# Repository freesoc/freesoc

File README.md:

freesoc
=======

freeSoC Board Layouts and Schematics

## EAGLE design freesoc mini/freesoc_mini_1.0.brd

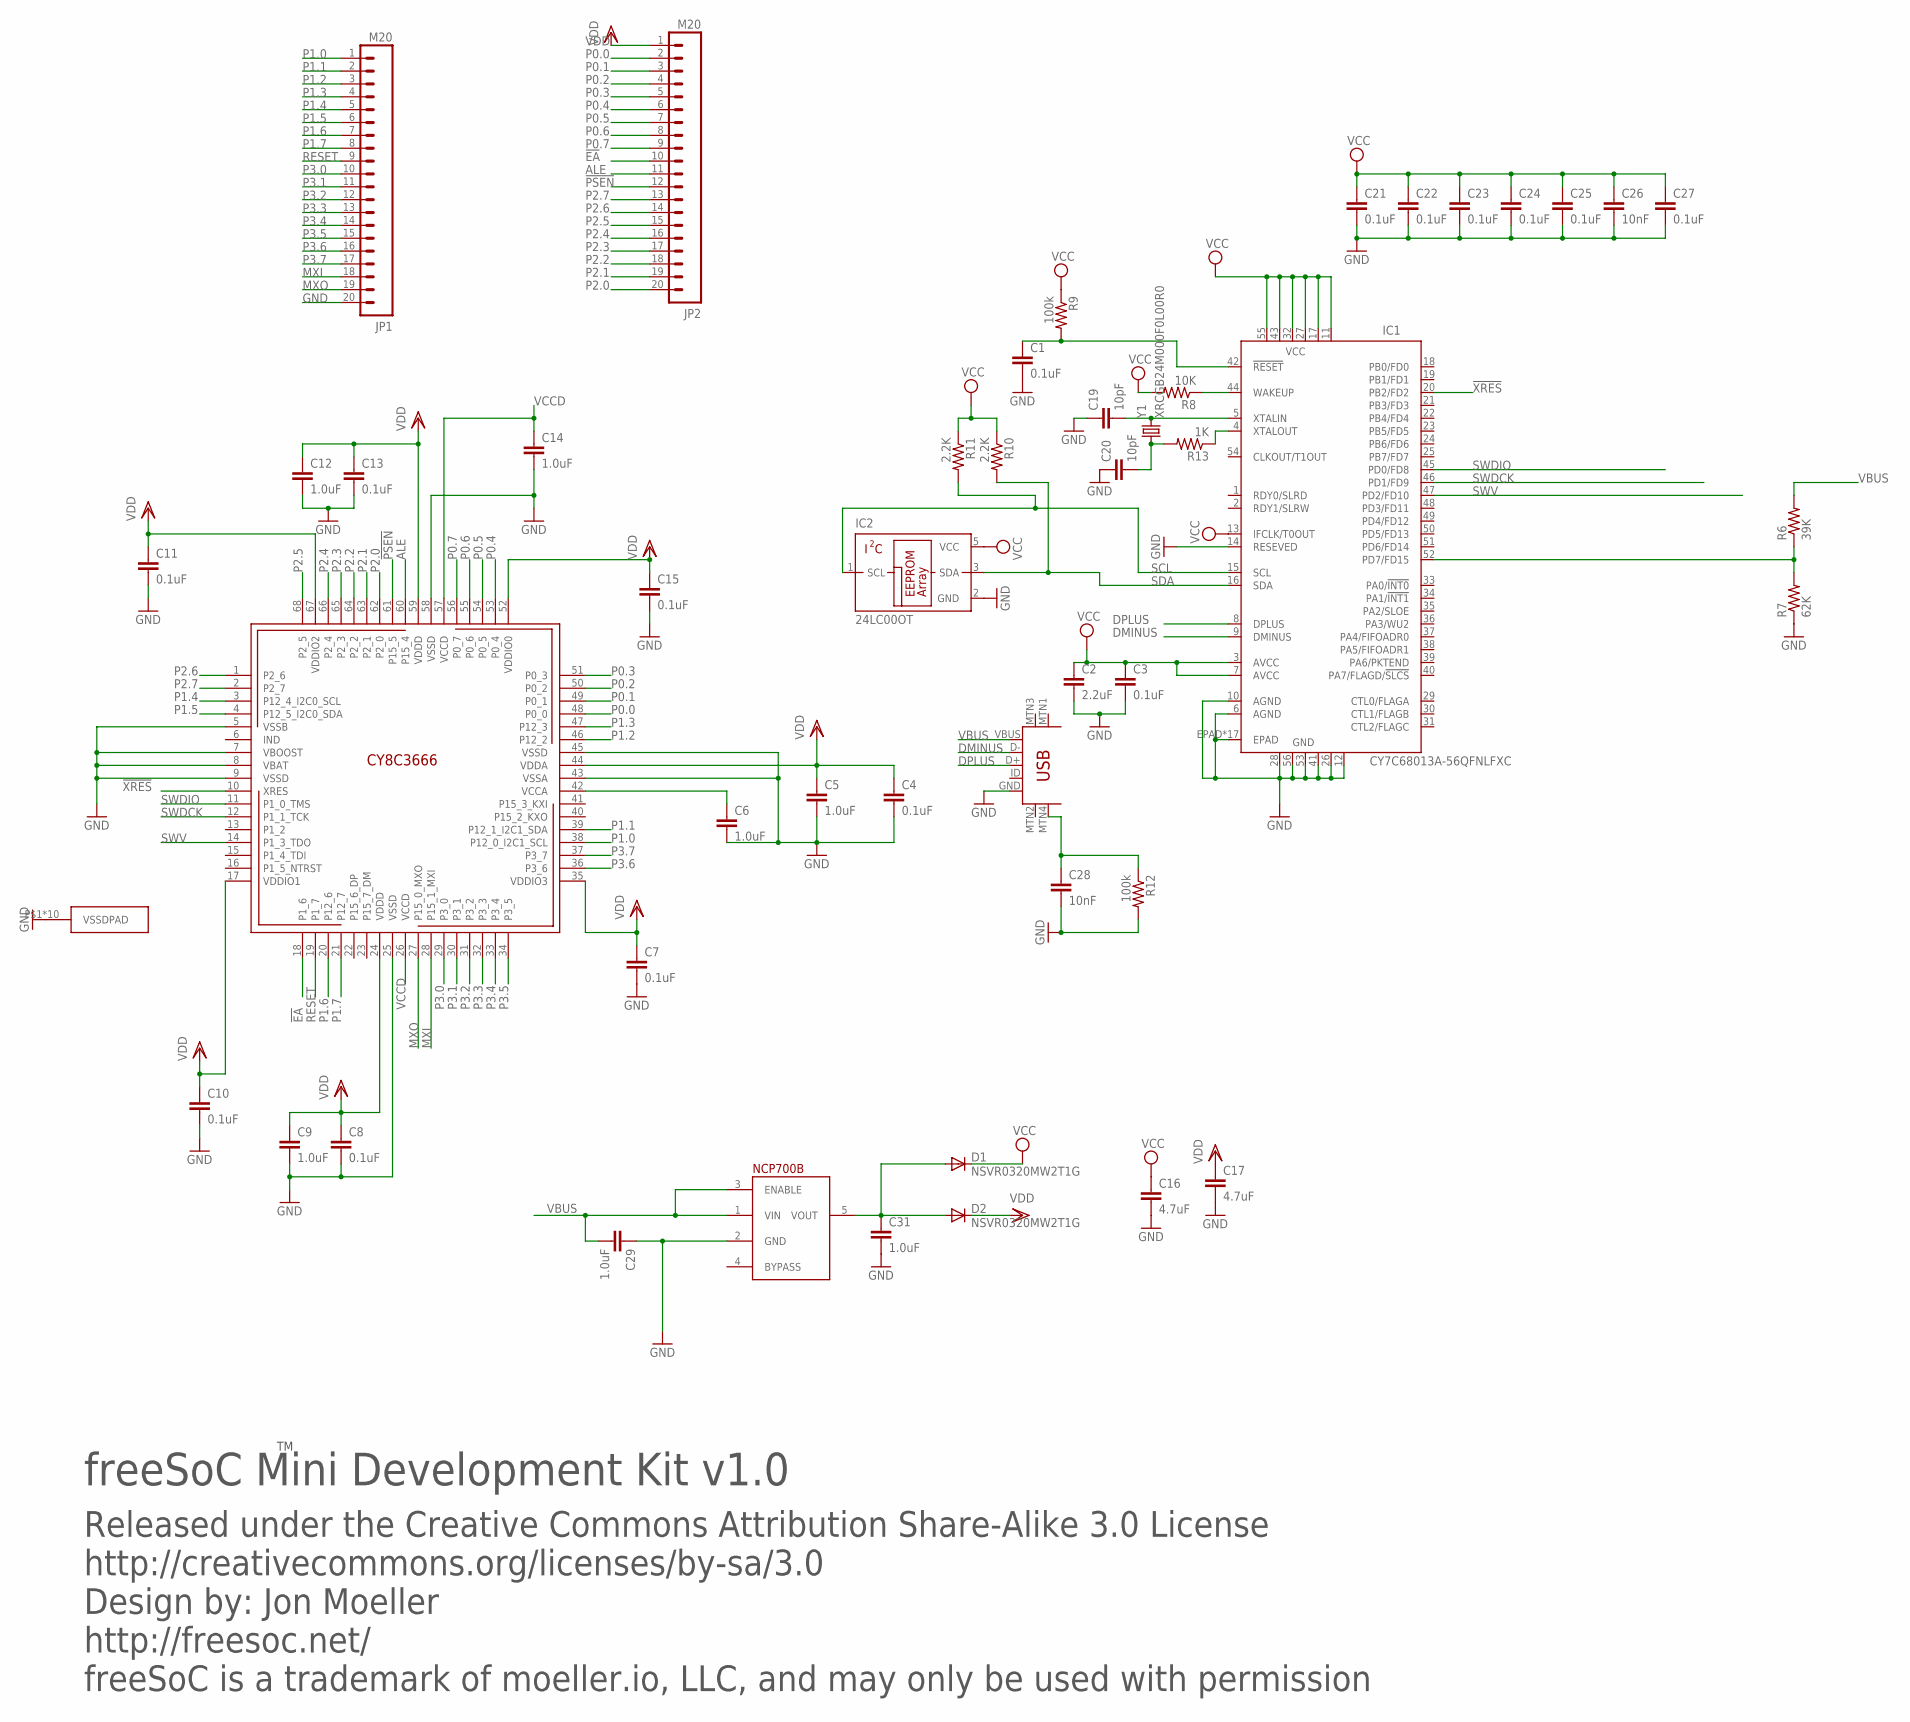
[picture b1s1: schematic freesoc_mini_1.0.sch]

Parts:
C1, C3, C4, C7, C8, C10, C11, C13, C15, C21, C22, C23, C24, C25, C27: 0.1uF; 0402-CAP
C2: 2.2uF; 0402-CAP
C5, C6, C9, C12, C14, C29, C31: 1.0uF; 0402-CAP
C16, C17: 4.7uF; 0603-CAP
C19, C20: 10pF; 0402-CAP
C26, C28: 10nF; 0402-CAP
D1, D2: NSVR0320MW2T1G; SOD-323
IC1: CY7C68013A-56QFNLFXC; QFN56
IC2: 24LC00OT; SOT23-5L
JP1, JP2: M20; 1X20
R6: 39K; 0402-RES
R7: 62K; 0402-RES
R8: 10K; 0402-RES
R9, R12: 100k; 0402-RES
R10, R11: 2.2K; 0402-RES
R13: 1K; 0402-RES
U$1: CY8C3X66LTI; QFN-68
U$3: FAN2558S36X; TSOP-5
USB-MINIB: USB-MINIB-5PIN; USB-MINIB
Y1: XRCGB24M000F0L00R0; CRYSTAL_RESONATOR

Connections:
!EA: JP2.10, U$1.18 (P1_6)
!PSEN: JP2.12, U$1.61 (P15_5)
!XRES: IC1.20 (PB2/FD2), U$1.10 (XRES)
ALE: JP2.11, U$1.60 (P15_4)
DMINUS: IC1.9 (DMINUS), USB-MINIB.D-
DPLUS: IC1.8 (DPLUS), USB-MINIB.D+
GND: C1.2, C2.2, C3.2, C4.2, C5.2, C6.2, C7.2, C8.2, C9.2, C10.2, C11.2, C12.2, C13.2, C14.2, C15.2, C16.2, C17.2, C19.1, C20.1, C21.2, C22.2, C23.2, C24.2, C25.2, C26.2, C27.2, C28.2, C29.1, C31.2, IC1.6 (AGND), IC1.10 (AGND), IC1.12 (GND), IC1.14 (RESEVED), IC1.26 (GND), IC1.28 (GND), IC1.41 (GND), IC1.53 (GND), IC1.56 (GND), IC1.EPAD, IC1.P$1 (EPAD), IC1.P$2 (EPAD), IC1.P$3 (EPAD), IC1.P$4 (EPAD), IC1.P$5 (EPAD), IC1.P$6 (EPAD), IC1.P$7 (EPAD), IC1.P$8 (EPAD), IC1.P$9 (EPAD), IC1.P$10 (EPAD), IC1.P$11 (EPAD), IC1.P$12 (EPAD), IC1.P$13 (EPAD), IC1.P$14 (EPAD), IC1.P$15 (EPAD), IC1.P$16 (EPAD), IC2.2 (GND), JP1.20, R7.1, R12.2, U$1.5 (VSSB), U$1.7 (VBOOST), U$1.8 (VBAT), U$1.9 (VSSD), U$1.25 (VSSD), U$1.43 (VSSA), U$1.45 (VSSD), U$1.58 (VSSD), U$1.P$1 (VSSDPAD), U$1.P$2 (VSSDPAD), U$1.P$3 (VSSDPAD), U$1.P$4 (VSSDPAD), U$1.P$5 (VSSDPAD), U$1.P$6 (VSSDPAD), U$1.P$7 (VSSDPAD), U$1.P$8 (VSSDPAD), U$1.P$9 (VSSDPAD), U$1.PAD (VSSDPAD), U$3.2 (GND), USB-MINIB.GND
MXI: JP1.18, U$1.28 (P15_1_MXI)
MXO: JP1.19, U$1.27 (P15_0_MXO)
unnamed: IC1.52 (PD7/FD15), R6.1, R7.2
unnamed: IC1.44 (WAKEUP), R8.1
unnamed: C1.1, IC1.42 (!RESET), R9.2
unnamed: C28.1, R12.1, USB-MINIB.MTN4
unnamed: IC1.4 (XTALOUT), R13.1
unnamed: C20.2, R13.2, Y1.P$1 (1)
unnamed: C19.2, IC1.5 (XTALIN), Y1.P$4 (2)
unnamed: C6.1, U$1.42 (VCCA)
P0.0: JP2.2, U$1.48 (P0_0)
P0.1: JP2.3, U$1.49 (P0_1)
P0.2: JP2.4, U$1.50 (P0_2)
P0.3: JP2.5, U$1.51 (P0_3)
P0.4: JP2.6, U$1.53 (P0_4)
P0.5: JP2.7, U$1.54 (P0_5)
P0.6: JP2.8, U$1.55 (P0_6)
P0.7: JP2.9, U$1.56 (P0_7)
P1.0: JP1.1, U$1.38 (P12_0_I2C1_SCL)
P1.1: JP1.2, U$1.39 (P12_1_I2C1_SDA)
P1.2: JP1.3, U$1.46 (P12_2)
P1.3: JP1.4, U$1.47 (P12_3)
P1.4: JP1.5, U$1.3 (P12_4_I2C0_SCL)
P1.5: JP1.6, U$1.4 (P12_5_I2C0_SDA)
P1.6: JP1.7, U$1.20 (P12_6)
P1.7: JP1.8, U$1.21 (P12_7)
P2.0: JP2.20, U$1.62 (P2_0)
P2.1: JP2.19, U$1.63 (P2_1)
P2.2: JP2.18, U$1.64 (P2_2)
P2.3: JP2.17, U$1.65 (P2_3)
P2.4: JP2.16, U$1.66 (P2_4)
P2.5: JP2.15, U$1.68 (P2_5)
P2.6: JP2.14, U$1.1 (P2_6)
P2.7: JP2.13, U$1.2 (P2_7)
P3.0: JP1.10, U$1.29 (P3_0)
P3.1: JP1.11, U$1.30 (P3_1)
P3.2: JP1.12, U$1.31 (P3_2)
P3.3: JP1.13, U$1.32 (P3_3)
P3.4: JP1.14, U$1.33 (P3_4)
P3.5: JP1.15, U$1.34 (P3_5)
P3.6: JP1.16, U$1.36 (P3_6)
P3.7: JP1.17, U$1.37 (P3_7)
RESET: JP1.9, U$1.19 (P1_7)
SCL: IC1.15 (SCL), IC2.1 (SCL), R11.2
SDA: IC1.16 (SDA), IC2.3 (SDA), R10.2
SWDCK: IC1.46 (PD1/FD9), U$1.12 (P1_1_TCK)
SWDIO: IC1.45 (PD0/FD8), U$1.11 (P1_0_TMS)
SWV: IC1.47 (PD2/FD10), U$1.14 (P1_3_TDO)
VBUS: C29.2, R6.2, U$3.1 (VIN), U$3.3 (ENABLE), USB-MINIB.VBUS
VCC: C2.1, C3.1, C16.1, C21.1, C22.1, C23.1, C24.1, C25.1, C26.1, C27.1, D1.1 (C), IC1.3 (AVCC), IC1.7 (AVCC), IC1.11 (VCC), IC1.13 (IFCLK/T0OUT), IC1.17 (VCC), IC1.27 (VCC), IC1.32 (VCC), IC1.43 (VCC), IC1.55 (VCC), IC2.5 (VCC), R8.2, R9.1, R10.1, R11.1
VCCD: C14.1, U$1.26 (VCCD), U$1.57 (VCCD)
VDD: C4.1, C5.1, C7.1, C8.1, C9.1, C10.1, C11.1, C12.1, C13.1, C15.1, C17.1, D2.1 (C), JP2.1, U$1.17 (VDDIO1), U$1.24 (VDDD), U$1.35 (VDDIO3), U$1.44 (VDDA), U$1.52 (VDDIO0), U$1.59 (VDDD), U$1.67 (VDDIO2)
VOUT: C31.1, D1.2 (A), D2.2 (A), U$3.5 (VOUT)

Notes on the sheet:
Released under the Creative Commons Attribution Share-Alike 3.0 License
http://creativecommons.org/licenses/by-sa/3.0
Design by: Jon Moeller
http://freesoc.net/
freeSoC is a trademark of moeller.io, LLC, and may only be used with permission
freeSoC Mini Development Kit v1.0

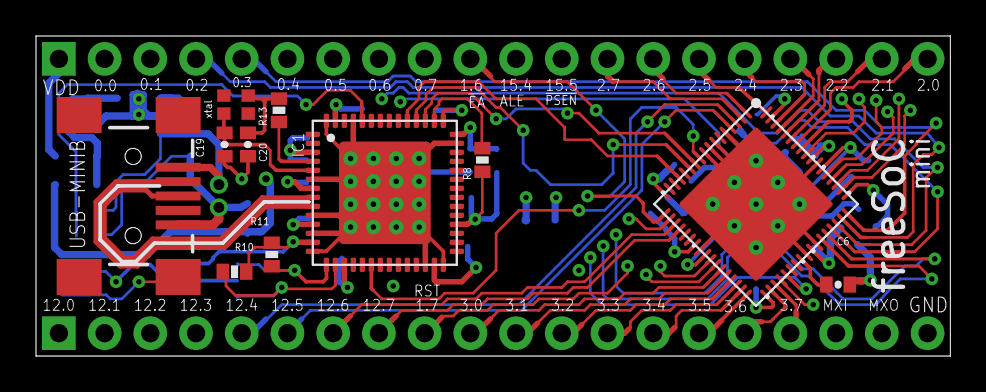
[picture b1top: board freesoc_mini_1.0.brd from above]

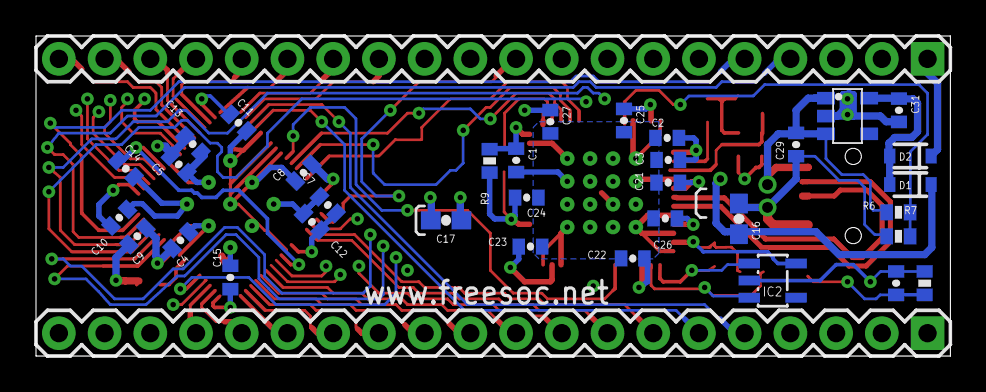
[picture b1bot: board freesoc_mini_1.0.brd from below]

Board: 4 copper layers, 50.8 x 17.8 mm, 47 parts (36 on the bottom side), 60 nets.

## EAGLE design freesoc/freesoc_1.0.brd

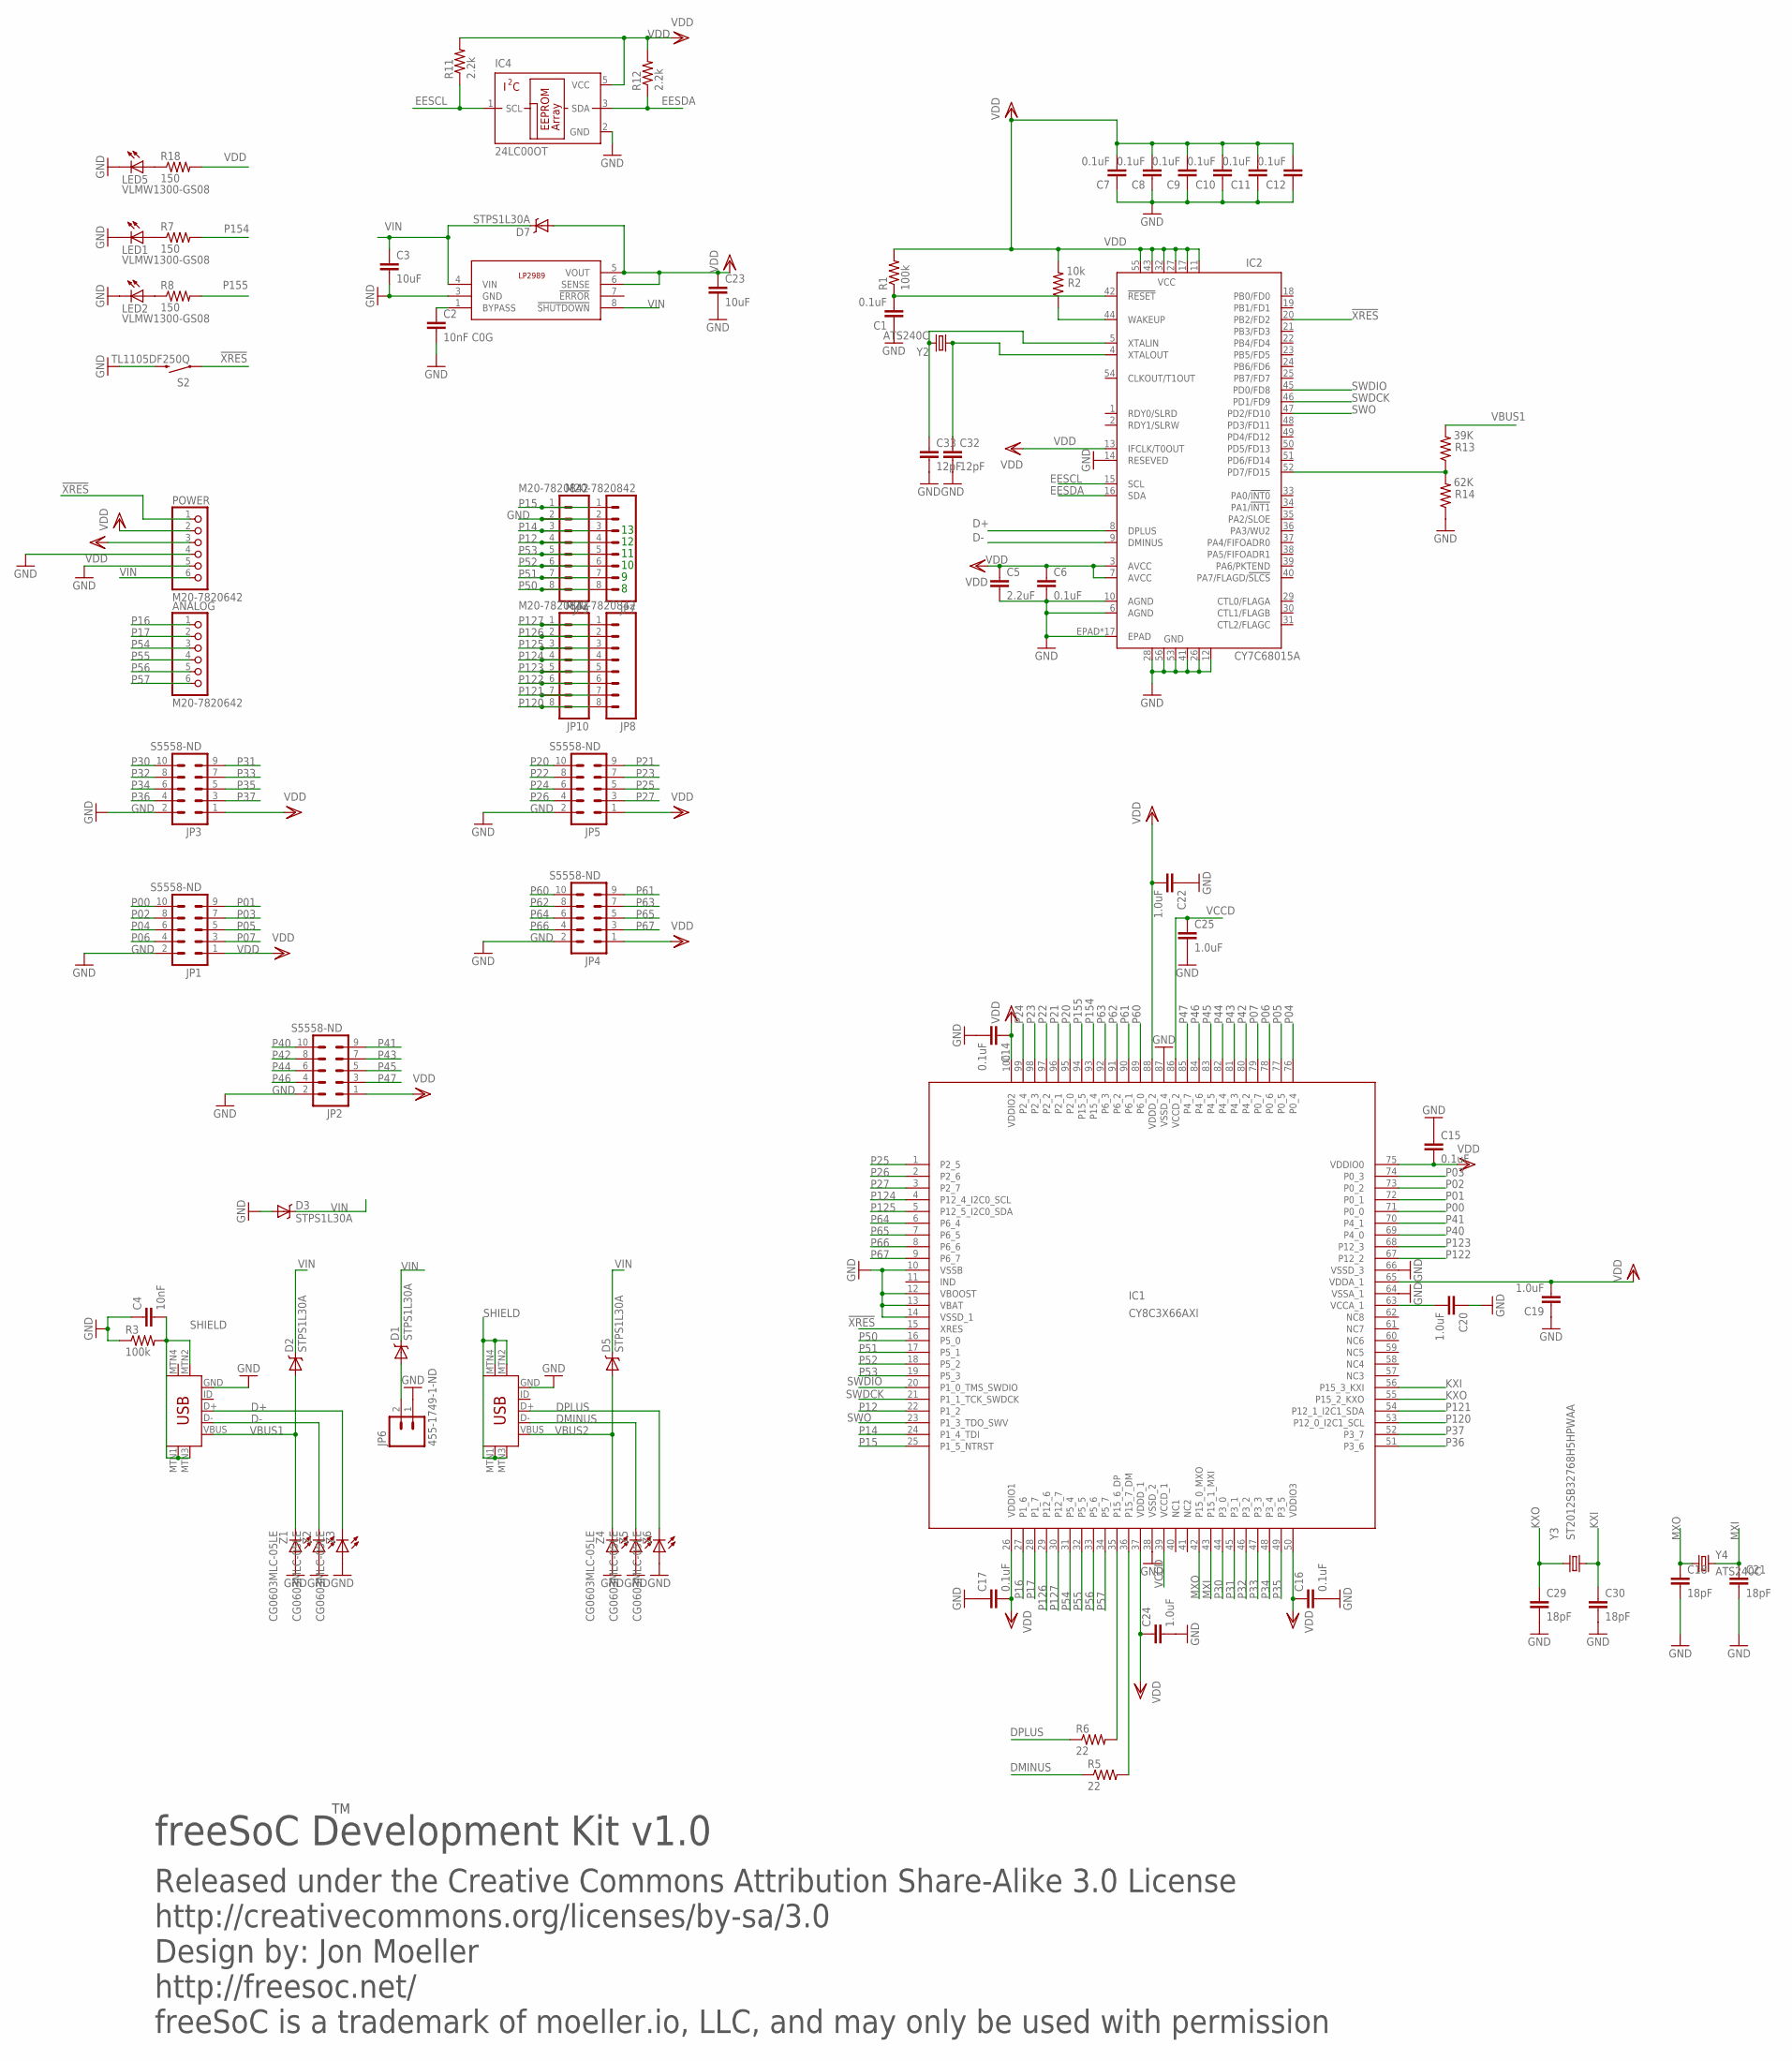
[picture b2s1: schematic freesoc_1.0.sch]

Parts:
ANALOG: M20-7820642; 1X06
C1, C6, C7, C8, C9, C10, C11, C12, C14, C15, C16, C17: 0.1uF; 0402-CAP
C2: 10nF C0G; 0402-CAP
C3, C23: 10uF; 1206
C4: 10nF; 0402-CAP
C5: 2.2uF; 0603-CAP
C18, C21, C29, C30: 18pF; 0402-CAP
C19, C20, C22, C24, C25: 1.0uF; 0402-CAP
C32, C33: 12pF; 0402-CAP
D1, D2, D3, D5, D7: STPS1L30A; SMA-DIODE
IC1: CY8C3X66AXI; TQFP-100
IC2: CY7C68015A; QFN56
IC4: 24LC00OT; SOT23-5L
JP1, JP2, JP3, JP4, JP5: S5558-ND; 2X5-RAF
JP6: 455-1749-1-ND; JST-2-SMD
JP7, JP8, JP9, JP10: M20-7820842; 1X08
LED1, LED2, LED5: VLMW1300-GS08; LED-0603
POWER: M20-7820642; 1X06
R1, R3: 100k; 0402-RES
R2: 10k; 0402-RES
R5, R6: 22; 0805
R7, R8, R18: 150; 0603-RES
R11, R12: 2.2k; 0402-RES
R13: 39K; 0402-RES
R14: 62K; 0402-RES
S2: TL1105DF250Q; TACTILE-PTH
U$1: LP2989; SO08
U$5, U$6: USB-MINIB-5PIN; USB-MINIB
Y2, Y4: ATS240C; HC49US
Y3: ST2012SB32768H5HPWAA; ST2012B
Z1, Z2, Z3, Z4, Z5, Z6: CG0603MLC-05LE; LED-0603

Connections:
!XRES: IC1.15 (XRES), IC2.20 (PB2/FD2), POWER.1, S2.1
D+: IC2.8 (DPLUS), U$5.D+, Z3.C
D-: IC2.9 (DMINUS), U$5.D-, Z2.C
DMINUS: R5.1, U$6.D-, Z5.C
DPLUS: R6.1, U$6.D+, Z6.C
EESCL: IC2.15 (SCL), IC4.1 (SCL), R11.1
EESDA: IC2.16 (SDA), IC4.3 (SDA), R12.1
GND: C1.1, C2.2, C3.2, C4.1, C5.2, C6.2, C7.1, C8.1, C9.1, C10.1, C11.1, C12.1, C14.2, C15.1, C16.2, C17.1, C18.2, C19.1, C20.1, C21.2, C22.1, C23.2, C24.2, C25.2, C29.2, C30.2, C32.2, C33.2, D3.A, IC1.10 (VSSB), IC1.12 (VBOOST), IC1.13 (VBAT), IC1.14 (VSSD_1), IC1.38 (VSSD_2), IC1.64 (VSSA_1), IC1.66 (VSSD_3), IC1.87 (VSSD_4), IC2.6 (AGND), IC2.10 (AGND), IC2.12 (GND), IC2.14 (RESEVED), IC2.26 (GND), IC2.28 (GND), IC2.41 (GND), IC2.53 (GND), IC2.56 (GND), IC2.EPAD, IC2.P$1 (EPAD), IC2.P$2 (EPAD), IC2.P$3 (EPAD), IC2.P$4 (EPAD), IC2.P$5 (EPAD), IC2.P$6 (EPAD), IC2.P$7 (EPAD), IC2.P$8 (EPAD), IC2.P$9 (EPAD), IC2.P$10 (EPAD), IC2.P$11 (EPAD), IC2.P$12 (EPAD), IC2.P$13 (EPAD), IC2.P$14 (EPAD), IC2.P$15 (EPAD), IC2.P$16 (EPAD), IC4.2 (GND), JP1.2, JP2.2, JP3.2, JP4.2, JP5.2, JP6.1, JP7.2, JP9.2, LED1.C, LED2.C, LED5.C, POWER.4, POWER.5, R3.1, R14.1, S2.3 (2), U$1.3 (GND), U$5.GND, U$6.GND, Z1.A, Z2.A, Z3.A, Z4.A, Z5.A, Z6.A
KXI: C30.1, IC1.56 (P15_3_KXI), Y3.P$2 (2)
KXO: C29.1, IC1.55 (P15_2_KXO), Y3.P$1 (1)
MXI: C21.1, IC1.43 (P15_1_MXI), Y4.2
MXO: C18.1, IC1.42 (P15_0_MXO), Y4.1
unnamed: C1.2, IC2.42 (!RESET), R1.1
unnamed: D1.A, JP6.2
unnamed: IC2.44 (WAKEUP), R2.1
unnamed: C20.2, IC1.63 (VCCA_1)
unnamed: IC1.35 (P15_6_DP), R6.2
unnamed: IC1.36 (P15_7_DM), R5.2
unnamed: LED1.A, R7.1
unnamed: LED2.A, R8.1
unnamed: C2.1, U$1.1 (BYPASS)
unnamed: IC2.52 (PD7/FD15), R13.1, R14.2
unnamed: LED5.A, R18.1
P00: IC1.71 (P0_0), JP1.10
P01: IC1.72 (P0_1), JP1.9
P02: IC1.73 (P0_2), JP1.8
P03: IC1.74 (P0_3), JP1.7
P04: IC1.76 (P0_4), JP1.6
P05: IC1.77 (P0_5), JP1.5
P06: IC1.78 (P0_6), JP1.4
P07: IC1.79 (P0_7), JP1.3
P12: IC1.22 (P1_2), JP7.4, JP9.4
P14: IC1.24 (P1_4_TDI), JP7.3, JP9.3
P15: IC1.25 (P1_5_NTRST), JP7.1, JP9.1
P16: ANALOG.1, IC1.27 (P1_6)
P17: ANALOG.2, IC1.28 (P1_7)
P20: IC1.95 (P2_0), JP5.10
P21: IC1.96 (P2_1), JP5.9
P22: IC1.97 (P2_2), JP5.8
P23: IC1.98 (P2_3), JP5.7
P24: IC1.99 (P2_4), JP5.6
P25: IC1.1 (P2_5), JP5.5
P26: IC1.2 (P2_6), JP5.4
P27: IC1.3 (P2_7), JP5.3
P30: IC1.44 (P3_0), JP3.10
P31: IC1.45 (P3_1), JP3.9
P32: IC1.46 (P3_2), JP3.8
P33: IC1.47 (P3_3), JP3.7
P34: IC1.48 (P3_4), JP3.6
P35: IC1.49 (P3_5), JP3.5
P36: IC1.51 (P3_6), JP3.4
P37: IC1.52 (P3_7), JP3.3
P40: IC1.69 (P4_0), JP2.10
P41: IC1.70 (P4_1), JP2.9
P42: IC1.80 (P4_2), JP2.8
P43: IC1.81 (P4_3), JP2.7
P44: IC1.82 (P4_4), JP2.6
P45: IC1.83 (P4_5), JP2.5
P46: IC1.84 (P4_6), JP2.4
P47: IC1.85 (P4_7), JP2.3
P50: IC1.16 (P5_0), JP7.8, JP9.8
P51: IC1.17 (P5_1), JP7.7, JP9.7
P52: IC1.18 (P5_2), JP7.6, JP9.6
P53: IC1.19 (P5_3), JP7.5, JP9.5
P54: ANALOG.3, IC1.31 (P5_4)
P55: ANALOG.4, IC1.32 (P5_5)
P56: ANALOG.5, IC1.33 (P5_6)
P57: ANALOG.6, IC1.34 (P5_7)
P60: IC1.89 (P6_0), JP4.10
P61: IC1.90 (P6_1), JP4.9
P62: IC1.91 (P6_2), JP4.8
P63: IC1.92 (P6_3), JP4.7
P64: IC1.6 (P6_4), JP4.6
P65: IC1.7 (P6_5), JP4.5
P66: IC1.8 (P6_6), JP4.4
P67: IC1.9 (P6_7), JP4.3
P120: IC1.53 (P12_0_I2C1_SCL), JP8.8, JP10.8
P121: IC1.54 (P12_1_I2C1_SDA), JP8.7, JP10.7
P122: IC1.67 (P12_2), JP8.6, JP10.6
P123: IC1.68 (P12_3), JP8.5, JP10.5
P124: IC1.4 (P12_4_I2C0_SCL), JP8.4, JP10.4
P125: IC1.5 (P12_5_I2C0_SDA), JP8.3, JP10.3
P126: IC1.29 (P12_6), JP8.2, JP10.2
P127: IC1.30 (P12_7), JP8.1, JP10.1
P154: IC1.93 (P15_4), R7.2
P155: IC1.94 (P15_5), R8.2
SHIELD: C4.2, R3.2, U$5.MTN1 (MTN2), U$5.MTN2 (MTN3), U$5.MTN3 (MTN1), U$6.MTN1 (MTN2), U$6.MTN2 (MTN3), U$6.MTN3 (MTN1), U$6.MTN4
SWDCK: IC1.21 (P1_1_TCK_SWDCK), IC2.46 (PD1/FD9)
SWDIO: IC1.20 (P1_0_TMS_SWDIO), IC2.45 (PD0/FD8)
SWO: IC1.23 (P1_3_TDO_SWV), IC2.47 (PD2/FD10)
VBUS1: D2.A, R13.2, U$5.VBUS, Z1.C
VBUS2: D5.A, U$6.VBUS, Z4.C
VCCD: C25.1, IC1.39 (VCCD_1), IC1.86 (VCCD_2)
VDD: C5.1, C6.1, C7.2, C8.2, C9.2, C10.2, C11.2, C12.2, C14.1, C15.2, C16.1, C17.2, C19.2, C22.2, C23.1, C24.1, D7.A, IC1.26 (VDDIO1), IC1.37 (VDDD_1), IC1.50 (VDDIO3), IC1.65 (VDDA_1), IC1.75 (VDDIO0), IC1.88 (VDDD_2), IC1.100 (VDDIO2), IC2.3 (AVCC), IC2.7 (AVCC), IC2.11 (VCC), IC2.13 (IFCLK/T0OUT), IC2.17 (VCC), IC2.27 (VCC), IC2.32 (VCC), IC2.43 (VCC), IC2.55 (VCC), IC4.5 (VCC), JP1.1, JP2.1, JP3.1, JP4.1, JP5.1, POWER.2, POWER.3, R1.2, R2.2, R11.2, R12.2, R18.2, U$1.5 (VOUT), U$1.6 (SENSE)
VIN: C3.1, D1.C, D2.C, D3.C, D5.C, D7.C, POWER.6, U$1.4 (VIN), U$1.8 (!SHUTDOWN)
XIN: C33.1, IC2.5 (XTALIN), Y2.2
XOUT: C32.1, IC2.4 (XTALOUT), Y2.1

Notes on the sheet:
Released under the Creative Commons Attribution Share-Alike 3.0 License
http://creativecommons.org/licenses/by-sa/3.0
Design by: Jon Moeller
http://freesoc.net/
freeSoC is a trademark of moeller.io, LLC, and may only be used with permission
freeSoC Development Kit v1.0

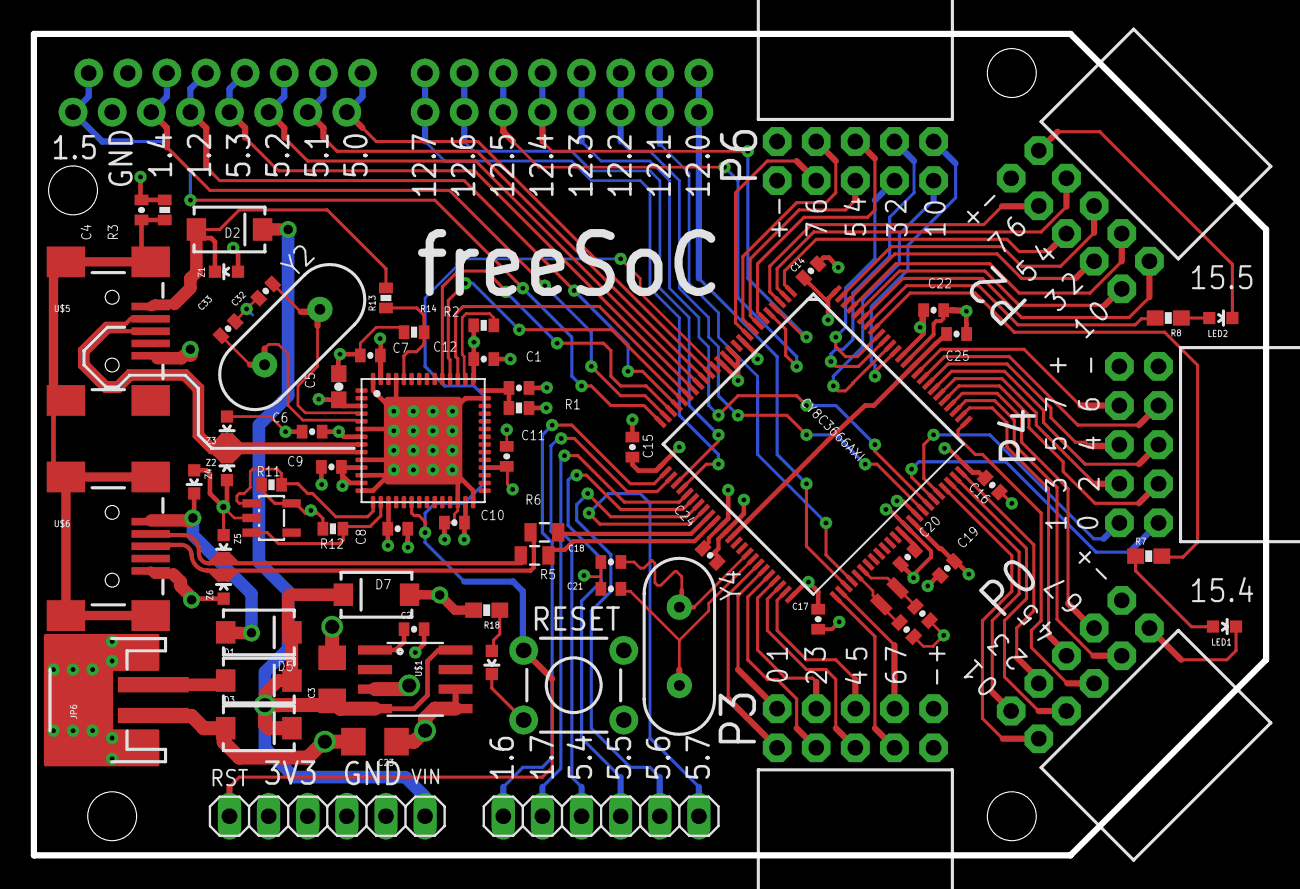
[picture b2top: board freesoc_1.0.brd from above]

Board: 4 copper layers, 80.0 x 53.3 mm, 76 parts (0 on the bottom side), 97 nets.

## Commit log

2012-09-07 Adding freeSoC and freeSoC Mini board designs and schematics
    Initial commit of board layouts and schematics
2012-09-07 Adding License
    Adding creative commons license text
2012-09-25 DFM changes to freeSoC
    Updated board for 7/7mil trace/space.
    All vias are now tented.
    Updated FX2 QFN pad land for improved reliability
2012-09-25 DFM changes to freesoc mini board
    All vias tented.
    Updated land pattern for FX2 and PSoC for improved reliability and
    smaller defect rate.
2012-09-25 More DFM changes
    Updated FX2 QFN package thermal pad dimensions to meet Cypress spec.
    Added tented vias on thermal pad, appropriate solder paste mask, and
    opened vias on bottom to eliminate outgassing
2012-09-25 More DFM changes for freesoc mini
    Updated FX2 QFN thermal pad to meet cypress spec.
    Updated PSoC QFN thermal pad to meet cypress spec.
    Added tented vias on thermal pad for both chips, proper solder paste
    stencil, and removed solder mask from bottom of vias to prevent
    outgassing.
2012-11-10 Changes for production
2013-01-12 Updates to boards for production
2013-02-28 Adding PDF Schematics

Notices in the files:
parts and their libraries:
SparkFun: Licensing: CC v3.0 Share-Alike You are welcome to use this library for commercial purposes.
